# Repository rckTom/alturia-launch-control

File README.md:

<p align="center">
  <picture>
    <source media="(prefers-color-scheme: dark)" srcset="design/logo/liftoff/alturia-launch-control-liftoff-reversed.svg">
    
  </picture>
</p>

# Alturia Launch Control

Alturia Launch Control is a wireless launch system for amateur rocketry.
You hold a handheld controller. At the pads stand up to eight satellites,
each with six channels for igniters or hybrid fill and vent valves, so one
controller handles up to 48 pads. Controller and satellites talk over an
encrypted LoRa link.

## Highlights

- **Four switches in series per channel.** Current flows through an igniter
  only when all four are closed: the key relay K2 (driven directly by the key
  switch on the satellite), the arm relay K1, the channel's high-side switch
  and its low-side MOSFET. Arming closes only K1. The two MOSFETs close
  together for the 1 s fire pulse and at no other time.
- **Self-test on arm.** The satellite detects welded relays and failed
  MOSFETs and refuses to arm a channel that fails.
- **Fails safe.** K1 is held by a monostable that the firmware has to
  retrigger every 80 ms, so a hung CPU drops it within about 150 ms. A
  satellite that hears nothing from the controller for 4 s goes SAFE. If the
  operator does nothing for 60 s, the controller disarms.
- **Precise continuity.** A test current of about 1.7 mA is measured with a
  24-bit ADC. That resolves a 1 to 2 Ω igniter from a short.
- **Secure radio link.** Pairing works like Bluetooth numeric comparison: an
  ECDH P-256 key exchange, then the operator checks that the LED pattern on
  the satellite matches the one on the controller's screen. After pairing,
  every frame is AES-128-CCM with replay protection. The link runs on
  869.85 MHz at 5 mW with no duty-cycle limit.
- **Field-ready hardware.** The controller has a sunlight-readable Sharp
  Memory LCD, a 1S LiPo and USB-C charging. The satellite sits in a
  waterproof 3D-printed case with an aluminium front panel and runs from a
  6 Ah LiFePO4 battery.

|          | Controller                         | Satellite                             |
|----------|------------------------------------|---------------------------------------|
| MCU      | ESP32-S3                           | STM32G474                             |
| Radio    | Wio-SX1262                         | Wio-SX1262                            |
| Firmware | Zephyr RTOS, LVGL UI               | Zephyr RTOS                           |
| Power    | 1S LiPo 4000 mAh, BQ24296M charger | LiFePO4 6 Ah                          |
| Display  | 400×240 Sharp Memory LCD           | 6 channel LEDs, status and armed LEDs |
| Controls | D-pad, ARM, FIRE, FILL, VENT, BACK | Key switch, continuity test button    |

## What's in the repo

```text
design/logo/     logo for this README and the controller splash screen
documentation/   write-ups: radio link, diagrams, photos
hardware/
  controller/    pcb/ KiCad and fab outputs, cad/ FreeCAD case, D-pad, panel art,
                 renders, sim/ FEM and SPICE checks
  satellite/     pcb/ KiCad and fab outputs, cad/ FreeCAD case, front panel, renders
  parts/         vendor 3D models and datasheets shared by both boards
firmware/
  controller/    operator console (ESP32-S3 or native_sim)
  satellite/     pad-side satellite (STM32G474)
  common/        LoRa backend, secure link, wire format, buzzer chime
  boards/        out-of-tree Zephyr boards alturia_controller, alturia_satellite
  lora_bench/    link bring-up on two Heltec WiFi LoRa 32 V4 boards
tools/radiosim/  radio network simulator with web UI
tools/webtool/   browser tool: firmware version, updates and shell over USB
```

Good places to start:

- [documentation/radio_link.md](documentation/radio_link.md): the radio
  link as implemented, covering pairing, keys, frame format, channel access
  and commands.
- [tools/radiosim/README.md](tools/radiosim/README.md): running the network
  without hardware.

## Status

Rev A of both boards has been built and is in bring-up. On the bench, the
satellite measures continuity and pairs with the controller over the air.
The controller firmware runs on its own hardware. The satellite's arm
state machine and command handling are still in progress. Nothing has flown
yet.

## Building

The firmware needs a Zephyr tree set up with `west`. It is developed
against upstream Zephyr main without patches; [`west.yml`](west.yml) pins
the revision and lists the modules it uses.

```sh
# Controller UI on the desktop, with an emulated display
west build -b native_sim firmware/controller && ./build/zephyr/zephyr.exe

# Controller hardware: MCUboot and the app, signed
west build --sysbuild -b alturia_controller/esp32s3/procpu -d build-board \
    firmware/controller -- -DBOARD_ROOT=$PWD/firmware
west flash -d build-board

# Satellite hardware; flashing over USB DFU: firmware/satellite/README.md
west build --sysbuild -b alturia_satellite -d build-board \
    firmware/satellite -- -DBOARD_ROOT=$PWD/firmware
```

With MCUboot on board, later updates can go through the browser:
[tools/webtool](tools/webtool/README.md) shows the firmware version,
installs new images over USB, and opens the shell.

For board-specific details, see
[firmware/satellite/README.md](firmware/satellite/README.md) and
[firmware/lora_bench/README.md](firmware/lora_bench/README.md).

## Safety

Alturia Launch Control fires pyrotechnic igniters. If you build or use it,
you do so at your own risk. The licenses below come without any warranty.
Follow the laws that apply to you and the safety rules of your range, and
test the system without igniters before you trust it at the pad.

## License

- Firmware and software (`firmware/`, `tools/`, `src/`): GNU General Public
  License v3.0 only, see [LICENSE](LICENSE).
- Hardware (`hardware/`): CERN Open Hardware Licence v2, strongly reciprocal,
  see [hardware/LICENSE](hardware/LICENSE).
- Documentation (`documentation/`):
  [CC BY-SA 4.0](https://creativecommons.org/licenses/by-sa/4.0/).
- The name "Alturia" and the logo in `design/logo/` are not covered by these
  licenses: all rights reserved, also where they appear in hardware files
  such as the front panel artwork.
- Third-party 3D models and drawings (`hardware/parts/` and vendor models in
  the PCB folders) remain under the terms of their owners.

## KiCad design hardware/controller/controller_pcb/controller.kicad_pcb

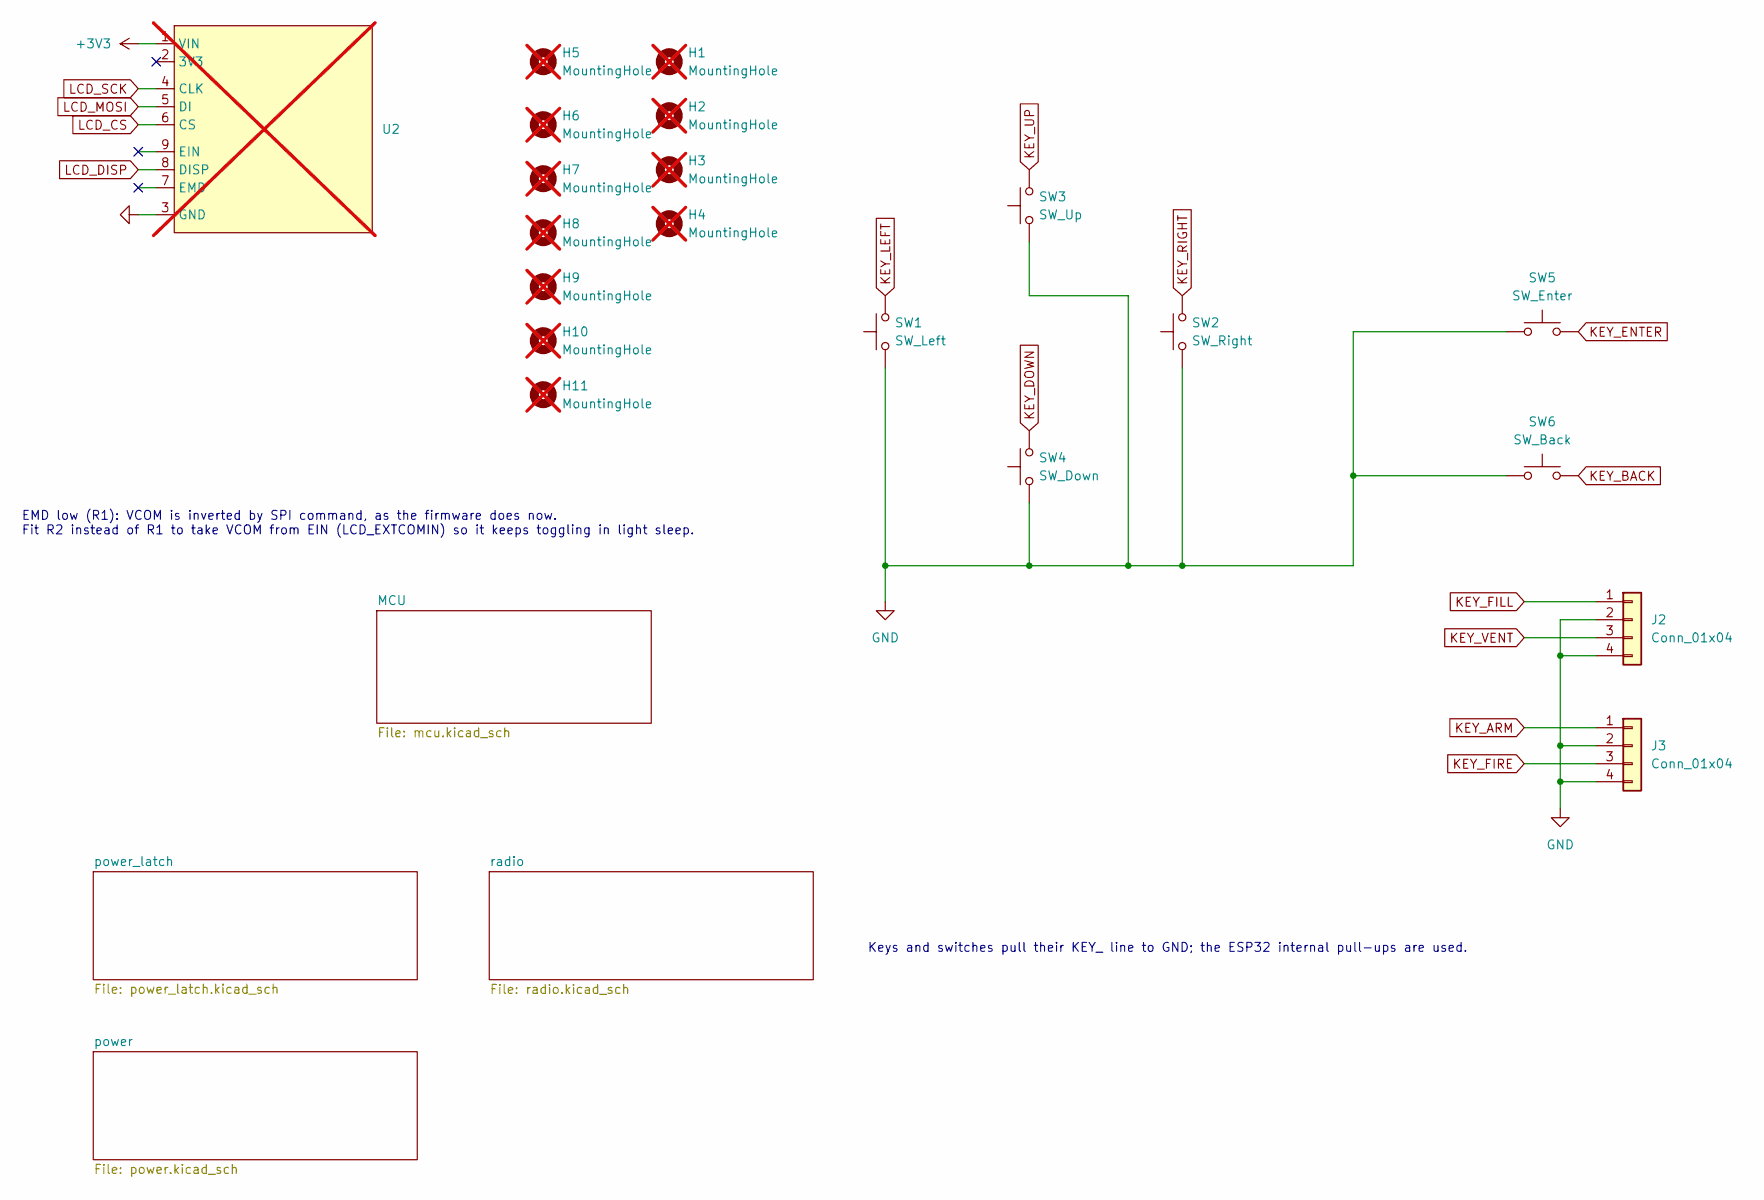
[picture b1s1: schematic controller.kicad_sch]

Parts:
H1, H2, H3, H4, H5, H6, H7, H8, H9, H10, H11: MountingHole; MountingHole_2.2mm_M2_ISO7380_Pad; not fitted
J2, J3: Conn_01x04; JST_PH_S4B-PH-K_1x04_P2.00mm_Horizontal; LCSC C157926
SW1: SW_Left; SW_Push_1P1T_XKB_TS-1187A; LCSC C318884
SW2: SW_Right; SW_Push_1P1T_XKB_TS-1187A; LCSC C318884
SW3: SW_Up; SW_Push_1P1T_XKB_TS-1187A; LCSC C318884
SW4: SW_Down; SW_Push_1P1T_XKB_TS-1187A; LCSC C318884
SW5: SW_Enter; SW_Push_1P1T_XKB_TS-1187A; LCSC C318884
SW6: SW_Back; SW_Push_1P1T_XKB_TS-1187A; LCSC C318884
U2: adafruit_memory_display_27; not fitted

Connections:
+3V3: U2.1 (VIN); also elsewhere on the board
GND: J2.2, J2.4, J3.2, J3.4, SW1.1, SW2.1, SW3.1, SW4.1, SW5.1, SW6.1, U2.3 (GND); also elsewhere on the board
KEY_ARM: J3.1; also elsewhere on the board
KEY_BACK: SW6.2; also elsewhere on the board
KEY_DOWN: SW4.2; also elsewhere on the board
KEY_ENTER: SW5.2; also elsewhere on the board
KEY_FILL: J2.1; also elsewhere on the board
KEY_FIRE: J3.3; also elsewhere on the board
KEY_LEFT: SW1.2; also elsewhere on the board
KEY_RIGHT: SW2.2; also elsewhere on the board
KEY_UP: SW3.2; also elsewhere on the board
KEY_VENT: J2.3; also elsewhere on the board
LCD_CS: U2.6 (CS); also elsewhere on the board
LCD_DISP: U2.8 (DISP); also elsewhere on the board
LCD_MOSI: U2.5 (DI); also elsewhere on the board
LCD_SCK: U2.4 (CLK); also elsewhere on the board

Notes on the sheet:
Keys and switches pull their KEY_ line to GND; the ESP32 internal pull-ups are used.
EMD low (R1): VCOM is inverted by SPI command, as the firmware does now. Fit R2 instead of R1 to take VCOM from EIN (LCD_EXTCOMIN) so it keeps toggling in light sleep.

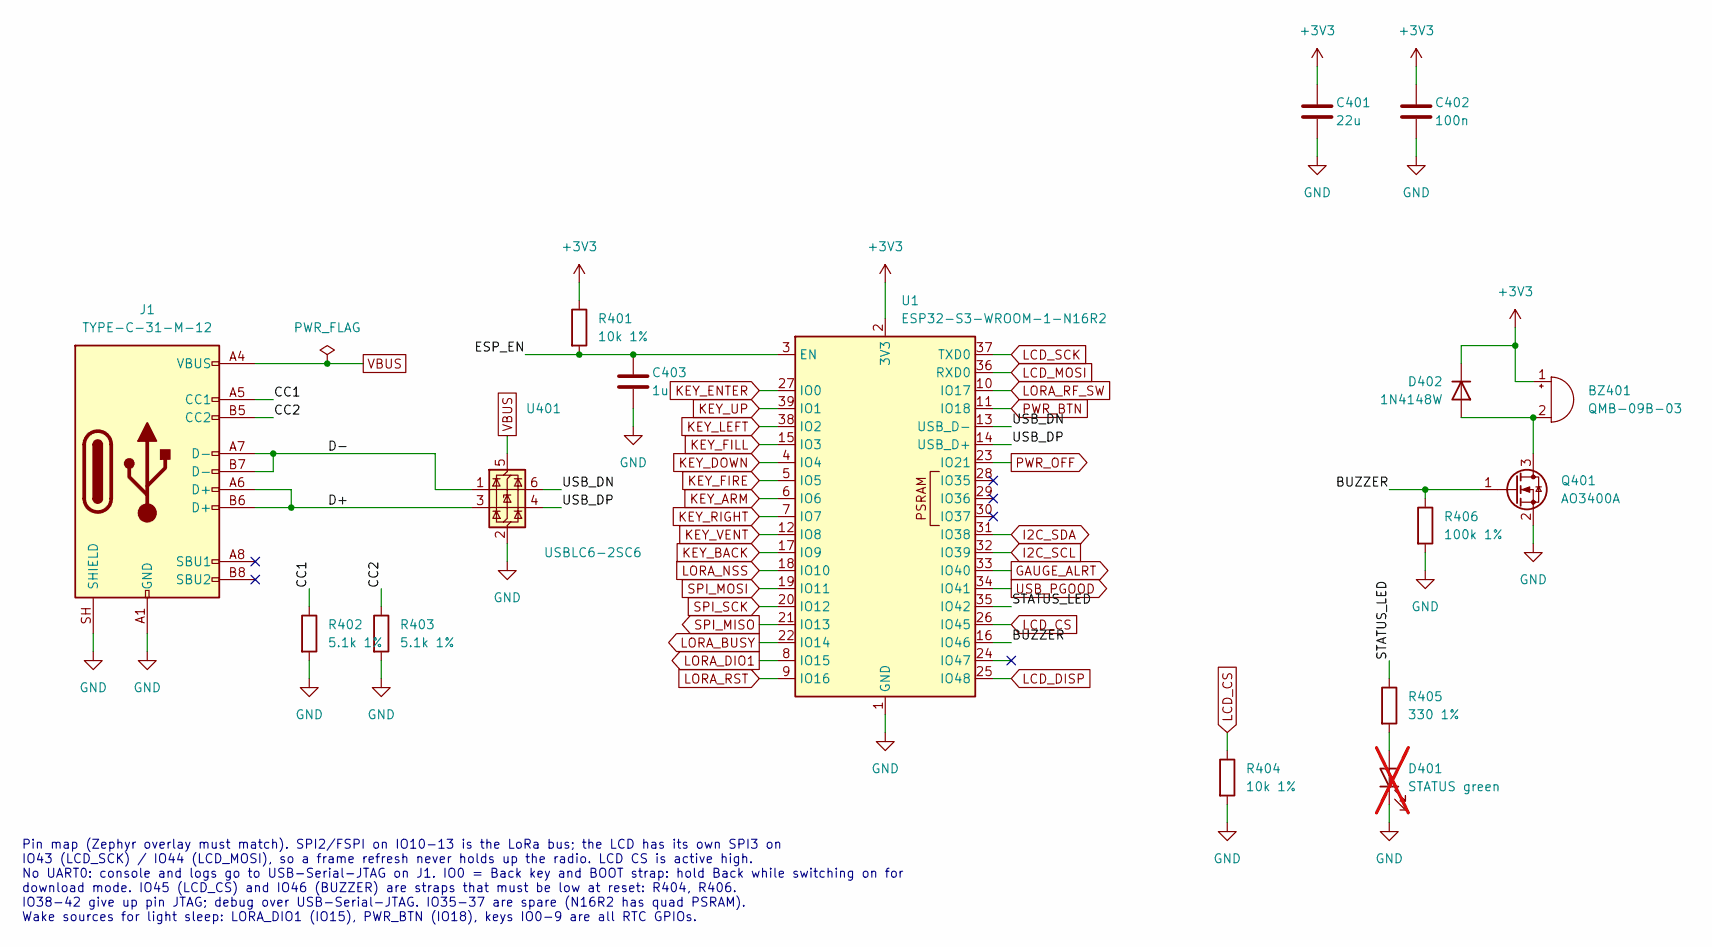
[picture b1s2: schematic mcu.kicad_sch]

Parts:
BZ401: QMB-09B-03; BUZ-TH_BD9.0-P4.00-D0.6-FD; LCSC C96256
C401: 22u; C_0603_1608Metric; LCSC C59461
C402: 100n; C_0603_1608Metric; LCSC C14663
C403: 1u; C_0603_1608Metric; LCSC C15849
D401: STATUS green; LED_D3.0mm; LCSC C12624; not fitted
D402: 1N4148W; D_SOD-123; LCSC C81598
J1: TYPE-C-31-M-12; USB_C_Receptacle_HRO_TYPE-C-31-M-12; LCSC C165948
Q401: AO3400A; SOT-23; LCSC C20917
R401, R404: 10k 1%; R_0603_1608Metric; LCSC C25804
R402, R403: 5.1k 1%; R_0603_1608Metric; LCSC C23186
R405: 330 1%; R_0603_1608Metric; LCSC C23138
R406: 100k 1%; R_0603_1608Metric; LCSC C25803
U1: ESP32-S3-WROOM-1-N16R2; ESP32-S3-WROOM-1; LCSC C2913205
U401: USBLC6-2SC6; SOT-23-6; LCSC C2687116

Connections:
+3V3: BZ401.1 (+), C401.1, C402.1, D402.1 (K), R401.1, U1.2 (3V3); also elsewhere on the board
/MCU/BUZZER: Q401.1 (G), R406.1, U1.16 (IO46)
/MCU/CC1: J1.A5 (CC1), R402.1
/MCU/CC2: J1.B5 (CC2), R403.1
/MCU/D+: J1.A6 (D+), J1.B6 (D+), U401.3 (I/O2)
/MCU/D-: J1.A7 (D-), J1.B7 (D-), U401.1 (I/O1)
/MCU/ESP_EN: C403.1, R401.2, U1.3 (EN)
/MCU/STATUS_LED: R405.1, U1.35 (IO42)
/MCU/USB_DN: U1.13 (USB_D-), U401.6 (I/O1)
/MCU/USB_DP: U1.14 (USB_D+), U401.4 (I/O2)
GAUGE_ALRT: U1.33 (IO40); also elsewhere on the board
GND: C401.2, C402.2, C403.2, D401.1 (K), J1.A1 (GND), J1.A12 (GND), J1.B1 (GND), J1.B12 (GND), J1.SH (SHIELD), Q401.2 (S), R402.2, R403.2, R404.2, R406.2, U1.1 (GND), U1.40 (GND), U1.41 (GND), U401.2 (GND); also elsewhere on the board
I2C_SCL: U1.32 (IO39); also elsewhere on the board
I2C_SDA: U1.31 (IO38); also elsewhere on the board
KEY_ARM: U1.6 (IO6); also elsewhere on the board
KEY_BACK: U1.17 (IO9); also elsewhere on the board
KEY_DOWN: U1.4 (IO4); also elsewhere on the board
KEY_ENTER: U1.27 (IO0); also elsewhere on the board
KEY_FILL: U1.15 (IO3); also elsewhere on the board
KEY_FIRE: U1.5 (IO5); also elsewhere on the board
KEY_LEFT: U1.38 (IO2); also elsewhere on the board
KEY_RIGHT: U1.7 (IO7); also elsewhere on the board
KEY_UP: U1.39 (IO1); also elsewhere on the board
KEY_VENT: U1.12 (IO8); also elsewhere on the board
LCD_CS: R404.1, U1.26 (IO45); also elsewhere on the board
LCD_DISP: U1.25 (IO48); also elsewhere on the board
LCD_MOSI: U1.36 (RXD0); also elsewhere on the board
LCD_SCK: U1.37 (TXD0); also elsewhere on the board
LORA_BUSY: U1.22 (IO14); also elsewhere on the board
LORA_DIO1: U1.8 (IO15); also elsewhere on the board
LORA_NSS: U1.18 (IO10); also elsewhere on the board
LORA_RF_SW: U1.10 (IO17); also elsewhere on the board
LORA_RST: U1.9 (IO16); also elsewhere on the board
unnamed: BZ401.2 (-), D402.2 (A), Q401.3 (D)
unnamed: D401.2 (A), R405.2
PWR_BTN: U1.11 (IO18); also elsewhere on the board
PWR_OFF: U1.23 (IO21); also elsewhere on the board
SPI_MISO: U1.21 (IO13); also elsewhere on the board
SPI_MOSI: U1.19 (IO11); also elsewhere on the board
SPI_SCK: U1.20 (IO12); also elsewhere on the board
USB_PGOOD: U1.34 (IO41); also elsewhere on the board
VBUS: J1.A4 (VBUS), J1.A9 (VBUS), J1.B4 (VBUS), J1.B9 (VBUS), U401.5 (VBUS); also elsewhere on the board

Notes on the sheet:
Pin map (Zephyr overlay must match). SPI2/FSPI on IO10-13 is the LoRa bus; the LCD has its own SPI3 on IO43 (LCD_SCK) / IO44 (LCD_MOSI), so a frame refresh never holds up the radio. LCD CS is active high. No UART0: console and logs go to USB-Serial-JTAG on J1. IO0 = Back key and BOOT strap: hold Ba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

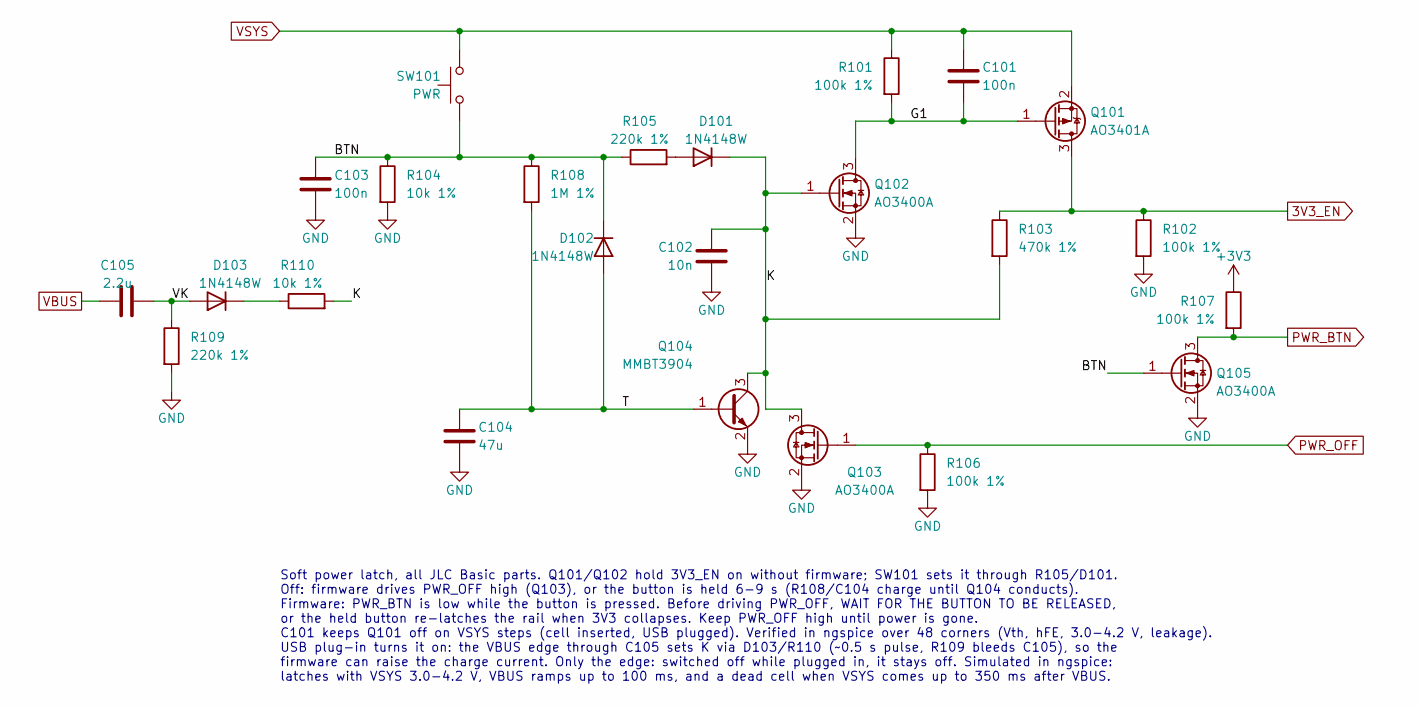
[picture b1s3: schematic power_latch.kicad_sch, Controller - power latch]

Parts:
C101, C103: 100n; C_0603_1608Metric; LCSC C14663
C102: 10n; C_0603_1608Metric; LCSC C57112
C104: 47u; C_0603_1608Metric; LCSC C140782
C105: 2.2u; C_0603_1608Metric; LCSC C23630
D101, D102, D103: 1N4148W; D_SOD-123; LCSC C81598
Q101: AO3401A; SOT-23; LCSC C15127
Q102, Q103, Q105: AO3400A; SOT-23; LCSC C20917
Q104: MMBT3904; SOT-23; LCSC C20526
R101, R102, R106, R107: 100k 1%; R_0603_1608Metric; LCSC C25803
R103: 470k 1%; R_0603_1608Metric; LCSC C23178
R104, R110: 10k 1%; R_0603_1608Metric; LCSC C25804
R105, R109: 220k 1%; R_0603_1608Metric; LCSC C22961
R108: 1M 1%; R_0603_1608Metric; LCSC C22935
SW101: PWR; SW_Push_1P1T-MP_NO_Horizontal_Alps_SKRTLAE010; LCSC C110293

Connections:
3V3_EN: Q101.3 (D), R102.1, R103.1; also elsewhere on the board
+3V3: R107.1; also elsewhere on the board
/power_latch/BTN: C103.1, D102.1 (K), Q105.1 (G), R104.1, R105.1, R108.1, SW101.1
/power_latch/G1: C101.2, Q101.1 (G), Q102.3 (D), R101.2
/power_latch/K: C102.1, D101.1 (K), Q102.1 (G), Q103.3 (D), Q104.3 (C), R103.2, R110.2
/power_latch/T: C104.1, D102.2 (A), Q104.1 (B), R108.2
/power_latch/VK: C105.2, D103.2 (A), R109.1
GND: C102.2, C103.2, C104.2, Q102.2 (S), Q103.2 (S), Q104.2 (E), Q105.2 (S), R102.2, R104.2, R106.2, R109.2; also elsewhere on the board
unnamed: D101.2 (A), R105.2
unnamed: D103.1 (K), R110.1
PWR_BTN: Q105.3 (D), R107.2; also elsewhere on the board
PWR_OFF: Q103.1 (G), R106.1; also elsewhere on the board
VBUS: C105.1; also elsewhere on the board
VSYS: C101.1, Q101.2 (S), R101.1, SW101.2; also elsewhere on the board

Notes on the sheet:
Soft power latch, all JLC Basic parts. Q101/Q102 hold 3V3_EN on without firmware; SW101 sets it through R105/D101. Off: firmware drives PWR_OFF high (Q103), or the button is held 6-9 s (R108/C104 charge until Q104 conducts). Firmware: PWR_BTN is low while the button is pressed. Before driving PWR_O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

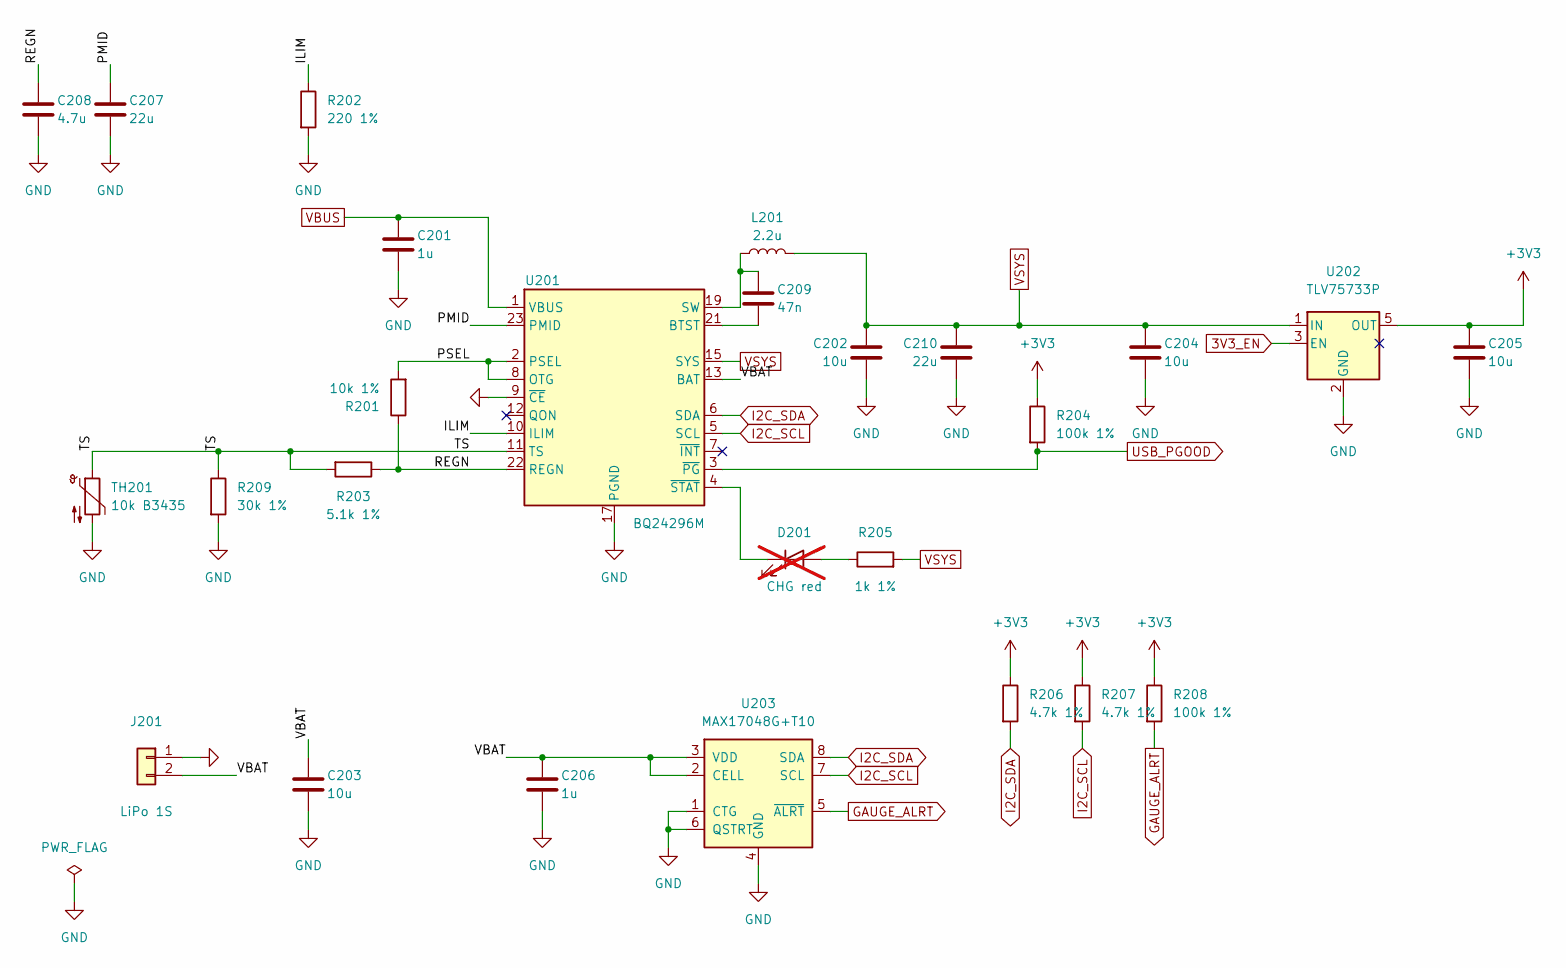
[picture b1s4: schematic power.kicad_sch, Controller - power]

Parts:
C201, C206: 1u; C_0603_1608Metric; LCSC C15849
C202, C203, C204, C205: 10u; C_0603_1608Metric; LCSC C19702
C207, C210: 22u; C_0805_2012Metric; LCSC C45783
C208: 4.7u; C_0603_1608Metric; LCSC C19666
C209: 47n; C_0603_1608Metric; LCSC C1622
D201: CHG red; LED_D3.0mm; LCSC C2286; not fitted
J201: LiPo 1S; JST_PH_S2B-PH-K_1x02_P2.00mm_Horizontal; LCSC C173752
L201: 2.2u; L_Taiyo-Yuden_NR-40xx; LCSC C135262
R201: 10k 1%; R_0603_1608Metric; LCSC C25804
R202: 220 1%; R_0603_1608Metric; LCSC C22962
R203: 5.1k 1%; R_0603_1608Metric; LCSC C23186
R204, R208: 100k 1%; R_0603_1608Metric; LCSC C25803
R205: 1k 1%; R_0603_1608Metric; LCSC C21190
R206, R207: 4.7k 1%; R_0603_1608Metric; LCSC C23162
R209: 30k 1%; R_0603_1608Metric; LCSC C22984
TH201: 10k B3435; R_0603_1608Metric; LCSC C2889048
U201: BQ24296M; Texas_RGE0024H_VQFN-24-1EP_4x4mm_P0.5mm_EP2.7x2.7mm_Thermal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; LCSC C130450
U202: TLV75733P; SOT-23-5; LCSC C485517
U203: MAX17048G+T10; TDFN-8-1EP_2x2mm_P0.5mm_EP0.8x1.2mm; LCSC C2682616

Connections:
3V3_EN: U202.3 (EN); also elsewhere on the board
+3V3: C205.1, R204.1, R206.1, R207.1, R208.1, U202.5 (OUT); also elsewhere on the board
/power/ILIM: R202.1, U201.10 (ILIM)
/power/PMID: C207.1, U201.23 (PMID)
/power/PSEL: R201.2, U201.2 (PSEL), U201.8 (OTG)
/power/REGN: C208.1, R201.1, R203.1, U201.22 (REGN)
/power/TS: R203.2, R209.1, TH201.1, U201.11 (TS)
/power/VBAT: C203.1, C206.1, J201.2, U201.13 (BAT), U201.14 (BAT), U203.2 (CELL), U203.3 (VDD)
GAUGE_ALRT: R208.2, U203.5 (~ALRT); also elsewhere on the board
GND: C201.2, C202.2, C203.2, C204.2, C205.2, C206.2, C207.2, C208.2, C210.2, J201.1, R202.2, R209.2, TH201.2, U201.9 (~CE), U201.17 (PGND), U201.18 (PGND), U201.25 (PGND), U202.2 (GND), U203.1 (CTG), U203.4 (GND), U203.6 (QSTRT), U203.9 (EP); also elsewhere on the board
I2C_SCL: R207.2, U201.5 (SCL), U203.7 (SCL); also elsewhere on the board
I2C_SDA: R206.2, U201.6 (SDA), U203.8 (SDA); also elsewhere on the board
unnamed: C209.1, L201.1, U201.19 (SW), U201.20 (SW)
unnamed: D201.2 (A), R205.1
unnamed: D201.1 (K), U201.4 (~STAT)
unnamed: C209.2, U201.21 (BTST)
USB_PGOOD: R204.2, U201.3 (~PG); also elsewhere on the board
VBUS: C201.1, U201.1 (VBUS), U201.24 (VBUS); also elsewhere on the board
VSYS: C202.1, C204.1, C210.1, L201.2, R205.2, U201.15 (SYS), U201.16 (SYS), U202.1 (IN); also elsewhere on the board

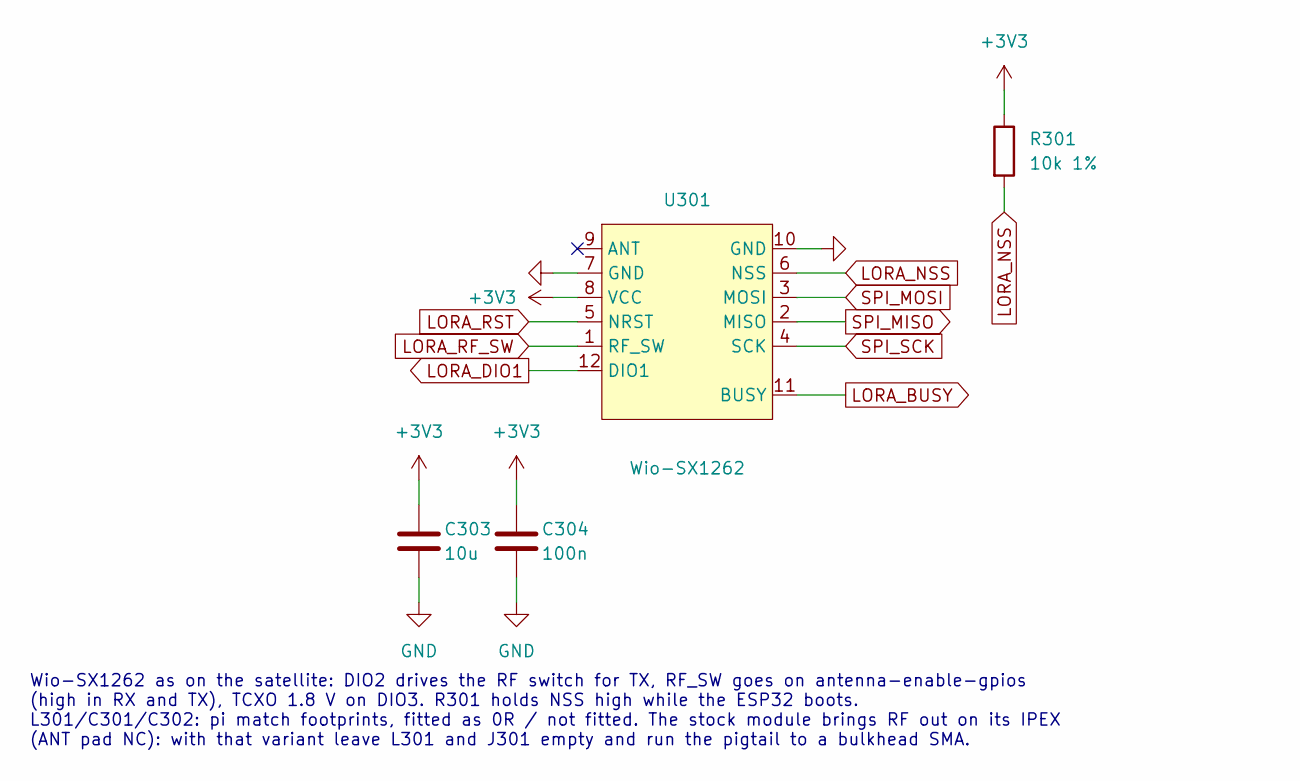
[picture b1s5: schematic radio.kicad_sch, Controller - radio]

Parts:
C303: 10u; C_0603_1608Metric; LCSC C19702
C304: 100n; C_0603_1608Metric; LCSC C14663
R301: 10k 1%; R_0603_1608Metric; LCSC C25804
U301: Wio-SX1262; WIRELM-SMD_WIO-SX1262

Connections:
+3V3: C303.1, C304.1, R301.1, U301.8 (VCC); also elsewhere on the board
GND: C303.2, C304.2, U301.7 (GND), U301.10 (GND); also elsewhere on the board
LORA_BUSY: U301.11 (BUSY); also elsewhere on the board
LORA_DIO1: U301.12 (DIO1); also elsewhere on the board
LORA_NSS: R301.2, U301.6 (NSS); also elsewhere on the board
LORA_RF_SW: U301.1 (RF_SW); also elsewhere on the board
LORA_RST: U301.5 (NRST); also elsewhere on the board
SPI_MISO: U301.2 (MISO); also elsewhere on the board
SPI_MOSI: U301.3 (MOSI); also elsewhere on the board
SPI_SCK: U301.4 (SCK); also elsewhere on the board

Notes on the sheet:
Wio-SX1262 as on the satellite: DIO2 drives the RF switch for TX, RF_SW goes on antenna-enable-gpios (high in RX and TX), TCXO 1.8 V on DIO3. R301 holds NSS high while the ESP32 boots. L301/C301/C302: pi match footprints, fitted as 0R / not fitted. The stock module brings RF out on its IPEX (ANT pa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

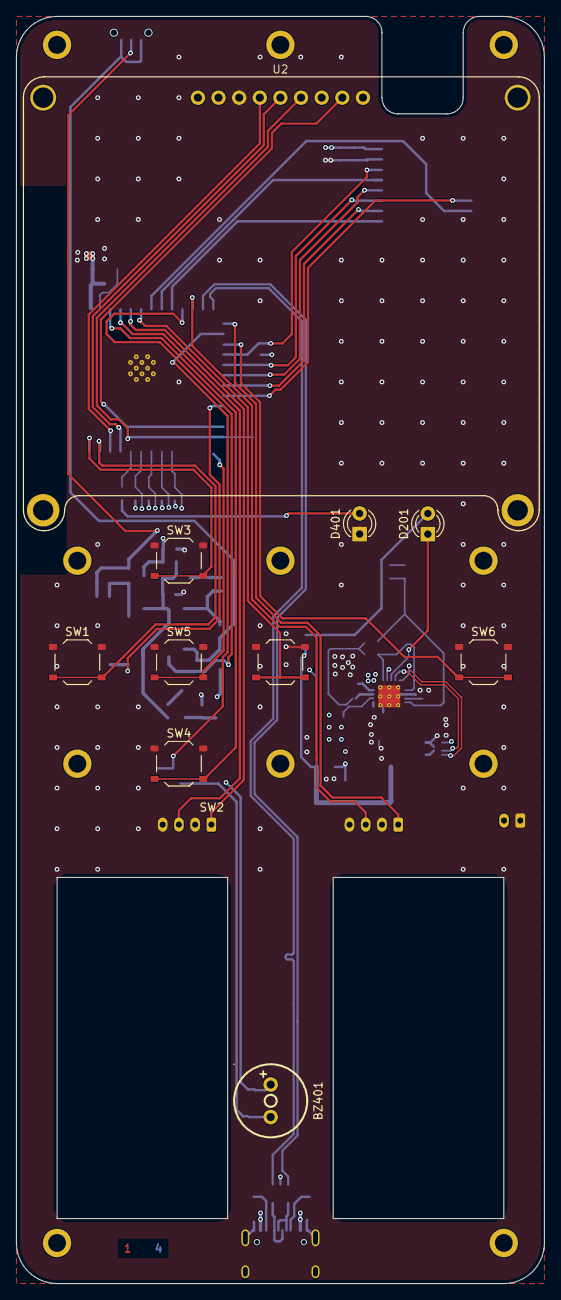
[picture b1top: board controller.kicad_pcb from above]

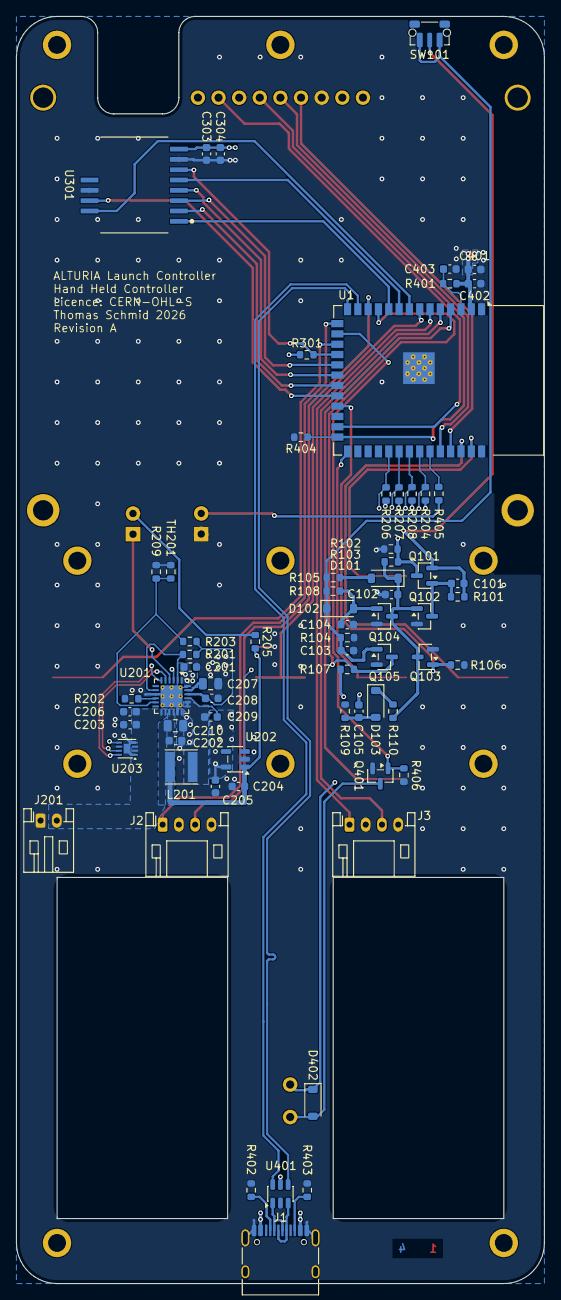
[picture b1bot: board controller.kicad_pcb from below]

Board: 4 copper layers, 65.0 x 156.0 mm, 90 parts (69 on the bottom side), 61 nets.

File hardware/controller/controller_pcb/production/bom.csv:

Designator,Footprint,Quantity,Value,LCSC Part #
BZ401,BUZ-TH_BD9.0-P4.00-D0.6-FD,1,QMB-09B-03,C96256
"C101, C103, C304, C402",0603,4,100n,C14663
C102,0603,1,10n,C57112
C104,0603,1,47u,C140782
C105,0603,1,2.2u,C23630
"C201, C206, C403",0603,3,1u,C15849
"C202, C203, C204, C205, C303",0603,5,10u,C19702
"C207, C210",0805,2,22u,C45783
C208,0603,1,4.7u,C19666
C209,0603,1,47n,C1622
C401,0603,1,22u,C59461
"D101, D102, D103, D402",D_SOD-123,4,1N4148W,C81598
J1,USB_C_Receptacle_HRO_TYPE-C-31-M-12,1,TYPE-C-31-M-12,C165948
"J2, J3",JST_PH_S4B-PH-K_1x04_P2.00mm_Horizontal,2,Conn_01x04,C157926
J201,JST_PH_S2B-PH-K_1x02_P2.00mm_Horizontal,1,LiPo 1S,C173752
L201,L_Taiyo-Yuden_NR-40xx,1,2.2u,C135262
Q101,SOT-23,1,AO3401A,C15127
"Q102, Q103, Q105, Q401",SOT-23,4,AO3400A,C20917
Q104,SOT-23,1,MMBT3904,C20526
"R101, R102, R106, R107, R204, R208, R406",0603,7,100k 1%,C25803
R103,0603,1,470k 1%,C23178
"R104, R110, R201, R301, R401, R404",0603,6,10k 1%,C25804
"R105, R109",0603,2,220k 1%,C22961
R108,0603,1,1M 1%,C22935
R202,0603,1,220 1%,C22962
"R203, R402, R403",0603,3,5.1k 1%,C23186
R205,0603,1,1k 1%,C21190
"R206, R207",0603,2,4.7k 1%,C23162
R209,0603,1,30k 1%,C22984
R405,0603,1,330 1%,C23138
SW1,SW_Push_1P1T_XKB_TS-1187A,1,SW_Left,C318884
SW101,SW_Push_1P1T-MP_NO_Horizontal_Alps_SKRTLAE010,1,PWR,C110293
SW2,SW_Push_1P1T_XKB_TS-1187A,1,SW_Right,C318884
SW3,SW_Push_1P1T_XKB_TS-1187A,1,SW_Up,C318884
SW4,SW_Push_1P1T_XKB_TS-1187A,1,SW_Down,C318884
SW5,SW_Push_1P1T_XKB_TS-1187A,1,SW_Enter,C318884
SW6,SW_Push_1P1T_XKB_TS-1187A,1,SW_Back,C318884
TH201,0603,1,10k B3435,C2889048
U1,ESP32-S3-WROOM-1,1,ESP32-S3-WROOM-1-N16R2,C2913205
U201,Texas_RGE0024H_VQFN-24-1EP_4x4mm_P0.5mm_EP2.7x2.7mm_ThermalVias,1,BQ24296M,C130450
U202,SOT-23-5,1,TLV75733P,C485517
U203,TDFN-8-1EP_2x2mm_P0.5mm_EP0.8x1.2mm,1,MAX17048G+T10,C2682616
U301,WIRELM-SMD_WIO-SX1262,1,Wio-SX1262,
U401,SOT-23-6,1,USBLC6-2SC6,C2687116

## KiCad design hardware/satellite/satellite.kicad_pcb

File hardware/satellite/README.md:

# Satellite board — KiCad project

Schematic for the pad-side satellite board.

**The schematic is hand-edited.** It was originally generated from a spec by a
script under `generator/`; that script has been removed and the sheets are now
edited in eeschema directly. Do not reintroduce a generator over these files —
regenerating would overwrite hand-drawn work. The spec is maintained to follow
the schematic, not the other way round.

## Status

Mid-migration from rev A to rev B. The output channel and the sense subsystem
have been redrawn; the power, MCU, radio and arm sheets have not. §19 of the spec
lists what is drawn, what is stubbed and what is miswired, and is derived from
the netlist rather than from reading the drawings.

## Verify

Close eeschema first — the exports below read the files, but `.lck` files present
mean someone has the project open and may be mid-edit.

```sh
cd hardware/satellite/pcb
kicad-cli sch erc --severity-all satellite.kicad_sch
kicad-cli sch export netlist --format kicadsexpr -o satellite.net satellite.kicad_sch
```

The netlist is the useful artefact: it resolves the six `output_channel`
instances and the root wiring between them, which is where the errors in spec §19
were found and where the next ones will be. Reading the sheets will not show you
that two stages are wired to the wrong rail.

ERC is not currently clean, and will not be until the two ADCs and the enable
lines are wired.

## Design parameters

`design.py` holds the shared numbers — pack voltage, divider values, ADC limits —
and `tests/` asserts the design criteria over them. It does **not** read the
schematic, so the two have to be kept in step by hand.

```sh
uv run --group hardware python -m pytest hardware/satellite/pcb/tests -q
```

A passing test is weaker evidence than it looks: the current one checks only the
ADC absolute maximum, not the measurable range, so it passes on a divider that
already saturates. See spec §16.13.

## Layout of the files

The KiCad project is in `pcb/`; paths below are relative to it unless they
start with `../`.

| File | Content |
|---|---|
| `satellite.kicad_sch` | Root: hierarchy, six channel instances |
| `01_power`, `02_mcu`, `03_radio`, `04_arm`, `06_sense_ui` | One sheet per spec section |
| `output_channel.kicad_sch` | Rev B output channel, instanced ×6 as `PyroStage1…6` |
| `05_channel.kicad_sch` | Rev A output channel. No longer instanced; kept for reference |
| `design.py`, `tests/` | Design parameters and checks over them |
| `library/` | LCSC symbols/footprints imported with `easyeda2kicad` |
| `production/` | Gerbers, ODB++, JLCPCB BOM and placement files |
| `../cad/` | FreeCAD case, front panel (engraving, UV DTF sheets), print meshes, renders |
| `../../parts/` | Vendor 3D models shared with the controller (also used as KiCad 3D models) |

Reference designators are grouped by sheet (2xx power, 3xx MCU, 4xx radio,
5xx arm, 12xx sense). The six channel instances use 6xx, 7xx, 8xx, 9xx, 13xx and
14xx — stage 1 is 14xx, stage 2 is 13xx, stages 3–6 are 6xx–9xx. That ordering is
an artefact of how the instances were created, not a scheme.

## Stale artefacts

`pcb/production/bom_jlcpcb.csv` was exported before the rev B channel
existed and describe the rev A design. No generator remains to re-export them;
regenerate from KiCad when the schematic settles.

Parts without an LCSC number are hand-fit: pin headers, tactile buttons, test
points (bare pads) and the not-fitted test headers.

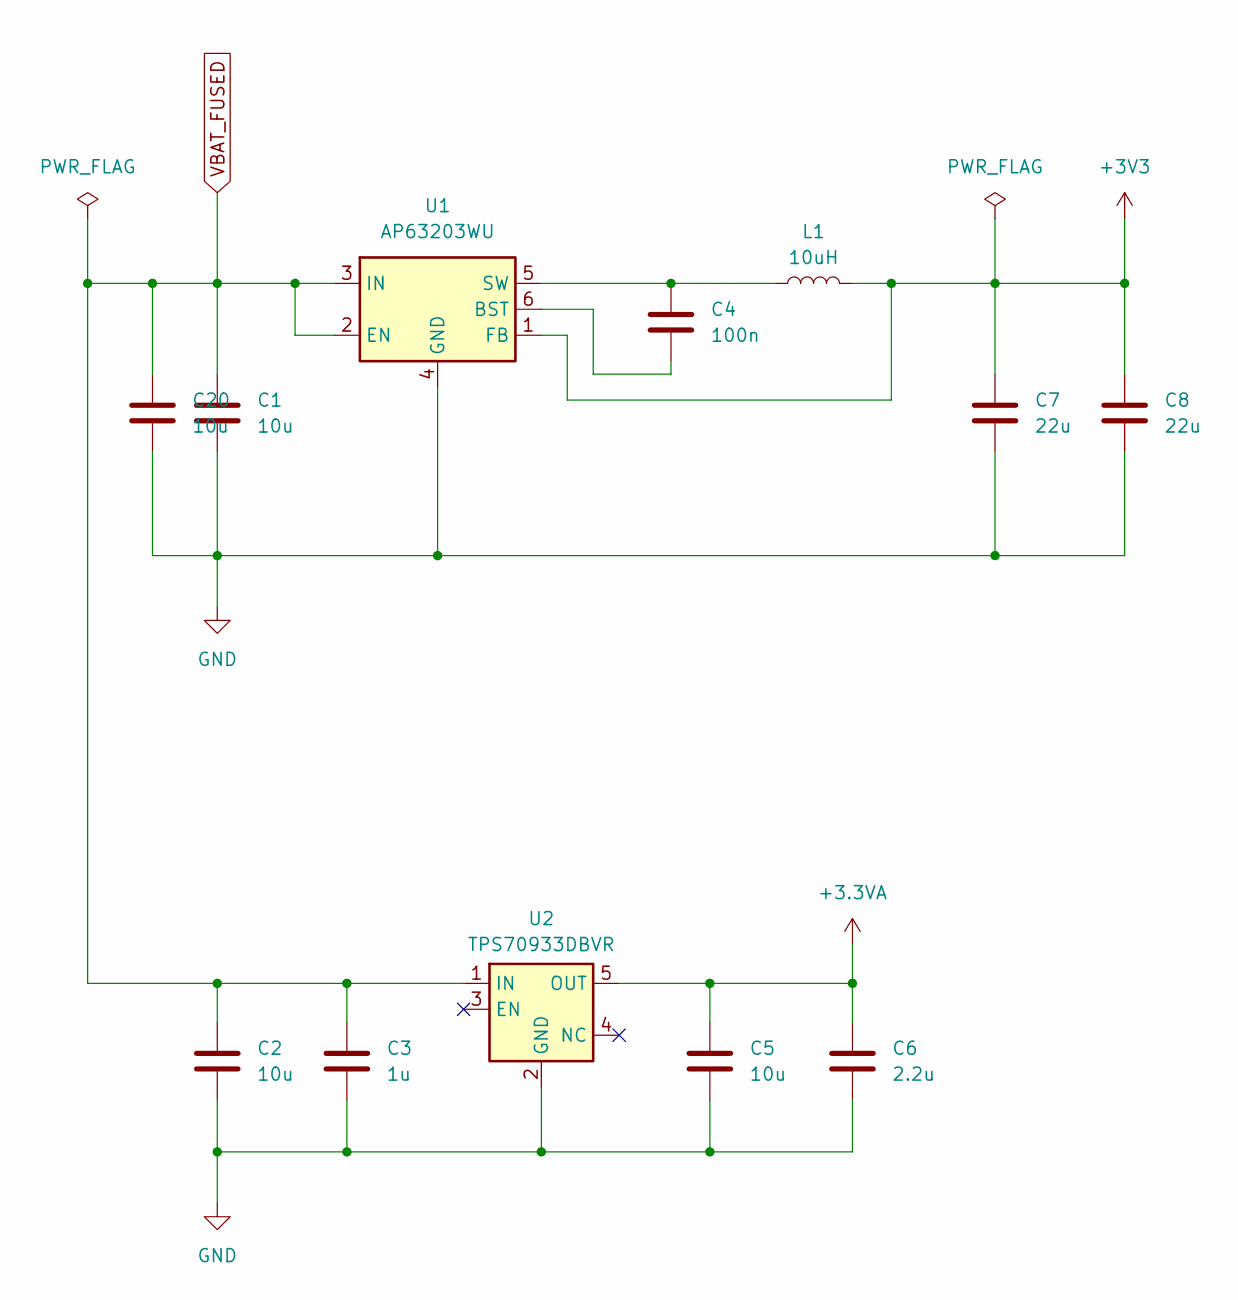
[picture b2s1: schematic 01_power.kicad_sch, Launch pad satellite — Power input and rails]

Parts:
C1, C2, C5, C20: 10u; C_0805_2012Metric; LCSC C440198
C3: 1u; C_0805_2012Metric; LCSC C28323
C4: 100n; C_0603_1608Metric; LCSC C14663
C6: 2.2u; C_0805_2012Metric; LCSC C19110
C7, C8: 22u; C_0805_2012Metric; LCSC C45783
L1: 10uH; L_Cenker_CKCS6045; LCSC C168076
U1: AP63203WU; TSOT-23-6; LCSC C780769
U2: TPS70933DBVR; SOT-23-5; LCSC C89347

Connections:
+3.3VA: C5.1, C6.1, U2.5 (OUT); also elsewhere on the board
+3V3: C7.1, C8.1, L1.2, U1.1 (FB); also elsewhere on the board
GND: C1.2, C2.2, C3.2, C5.2, C6.2, C7.2, C8.2, C20.2, U1.4 (GND), U2.2 (GND); also elsewhere on the board
unnamed: C4.2, U1.6 (BST)
unnamed: C4.1, L1.1, U1.5 (SW)
VBAT_FUSED: C1.1, C2.1, C3.1, C20.1, U1.2 (EN), U1.3 (IN), U2.1 (IN); also elsewhere on the board

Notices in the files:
firmware/boards/others/alturia_satellite/alturia_satellite_stm32g474xx.dts:
SPDX-License-Identifier: GPL-3.0-only
hardware/controller/controller_pcb/controller.kicad_pcb:
Licence: CERN-OHL-S
hardware/satellite/satellite.kicad_pcb:
© 2026 Thomas Schmid · CERN-OHL-S-2.0
